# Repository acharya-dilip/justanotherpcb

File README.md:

# Justanotherpcb
This is a PCB that holds chaos press the button to get a glimpse of what it holds and beware it may jump or rant at you

# Materials List:
LED's x6
Resistor (220) x6
Resistor (4.7k) x4
Resistor (47k) x2
Transistor (NPN) x2
Capacitor (10uf) x2
Push Switch x1
Mini Motor Disc x1
Buzzer x1
CR2032 Battery Cell x2

# What Does It DO?
This small fella is powered by two batteries and holds 6 LED's a mini motor disc and a buzzer. With the help of an astable multivibrator constatly switches between two states when power is provided and while the switcherooo occurs LED's in groups of 3 flash on and off while the motor and the buzzer also turn on in small bursts in sync with the groups of LED's.

# Some Glimpses

# Made By DILIP ACHARYA
Slack ID: acharyamission6
Made in a ADHD Hyperfocus state.
He'll spend the next month in recovery mode
Peace!

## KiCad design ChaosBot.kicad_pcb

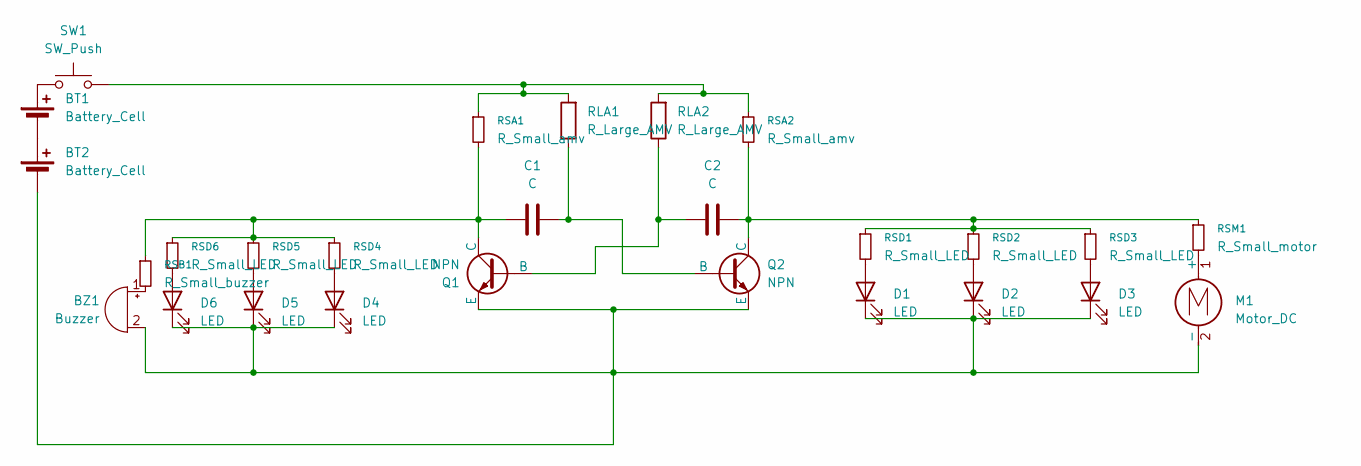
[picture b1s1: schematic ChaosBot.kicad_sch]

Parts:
BT1, BT2: Battery_Cell; BatteryHolder_Keystone_3034_1x20mm
BZ1: Buzzer; MagneticBuzzer_ProSignal_ABI-009-RC
C1, C2: C; CP_Radial_D8.0mm_P5.00mm
D1, D2, D3, D4, D5, D6: LED; LED_D5.0mm
M1: Motor_DC; PinHeader_1x02_P2.54mm_Vertical
Q1, Q2: NPN; TO-92L_HandSolder
RLA1, RLA2: R_Large_AMV; R_Axial_DIN0207_L6.3mm_D2.5mm_P7.62mm_Horizontal
RSA1, RSA2: R_Small_amv; R_Axial_DIN0207_L6.3mm_D2.5mm_P7.62mm_Horizontal
RSB1: R_Small_buzzer; R_Axial_DIN0207_L6.3mm_D2.5mm_P7.62mm_Horizontal
RSD1, RSD2, RSD3, RSD4, RSD5, RSD6: R_Small_LED; R_Axial_DIN0207_L6.3mm_D2.5mm_P7.62mm_Horizontal
RSM1: R_Small_motor; R_Axial_DIN0207_L6.3mm_D2.5mm_P7.62mm_Horizontal
SW1: SW_Push; SW_PUSH_6mm

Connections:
unnamed: BT1.1 (+), SW1.1
unnamed: BT1.2 (-), BT2.1 (+)
unnamed: BT2.2 (-), BZ1.2 (-), D1.1 (K), D2.1 (K), D3.1 (K), D4.1 (K), D5.1 (K), D6.1 (K), M1.2 (-), Q1.3 (E), Q2.3 (E)
unnamed: BZ1.1 (+), RSB1.2
unnamed: D1.2 (A), RSD1.2
unnamed: D2.2 (A), RSD2.2
unnamed: D3.2 (A), RSD3.2
unnamed: D4.2 (A), RSD4.2
unnamed: D5.2 (A), RSD5.2
unnamed: D6.2 (A), RSD6.2
unnamed: M1.1 (+), RSM1.2
unnamed: C2.1, Q1.2 (B), RLA2.1
unnamed: C1.1, Q1.1 (C), RSA1.2, RSB1.1, RSD4.1, RSD5.1, RSD6.1
unnamed: C1.2, Q2.2 (B), RLA1.1
unnamed: C2.2, Q2.1 (C), RSA2.2, RSD1.1, RSD2.1, RSD3.1, RSM1.1
unnamed: RLA1.2, RLA2.2, RSA1.1, RSA2.1, SW1.2

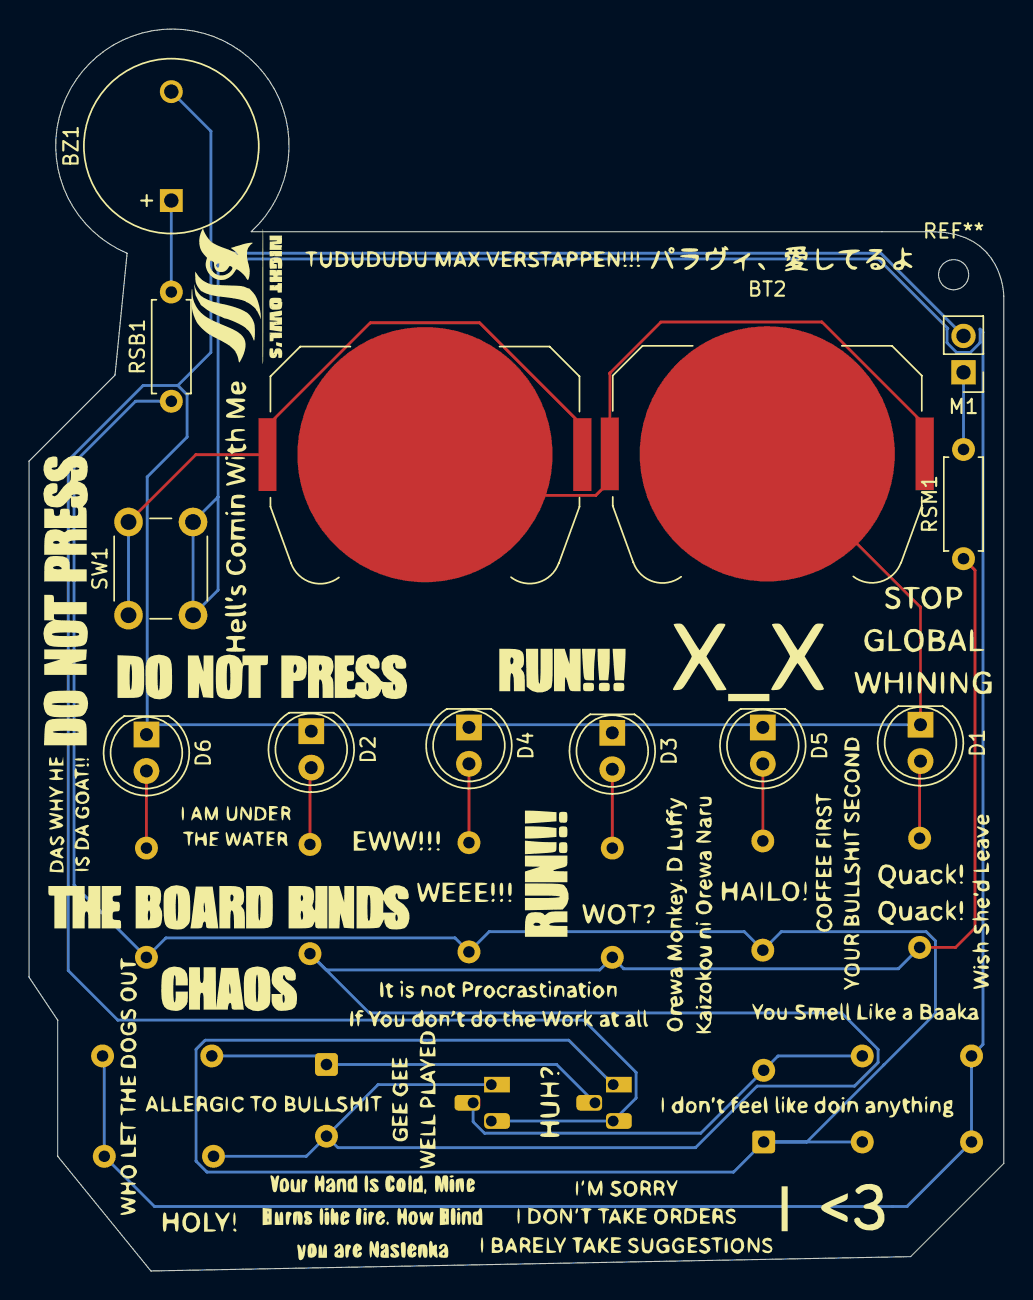
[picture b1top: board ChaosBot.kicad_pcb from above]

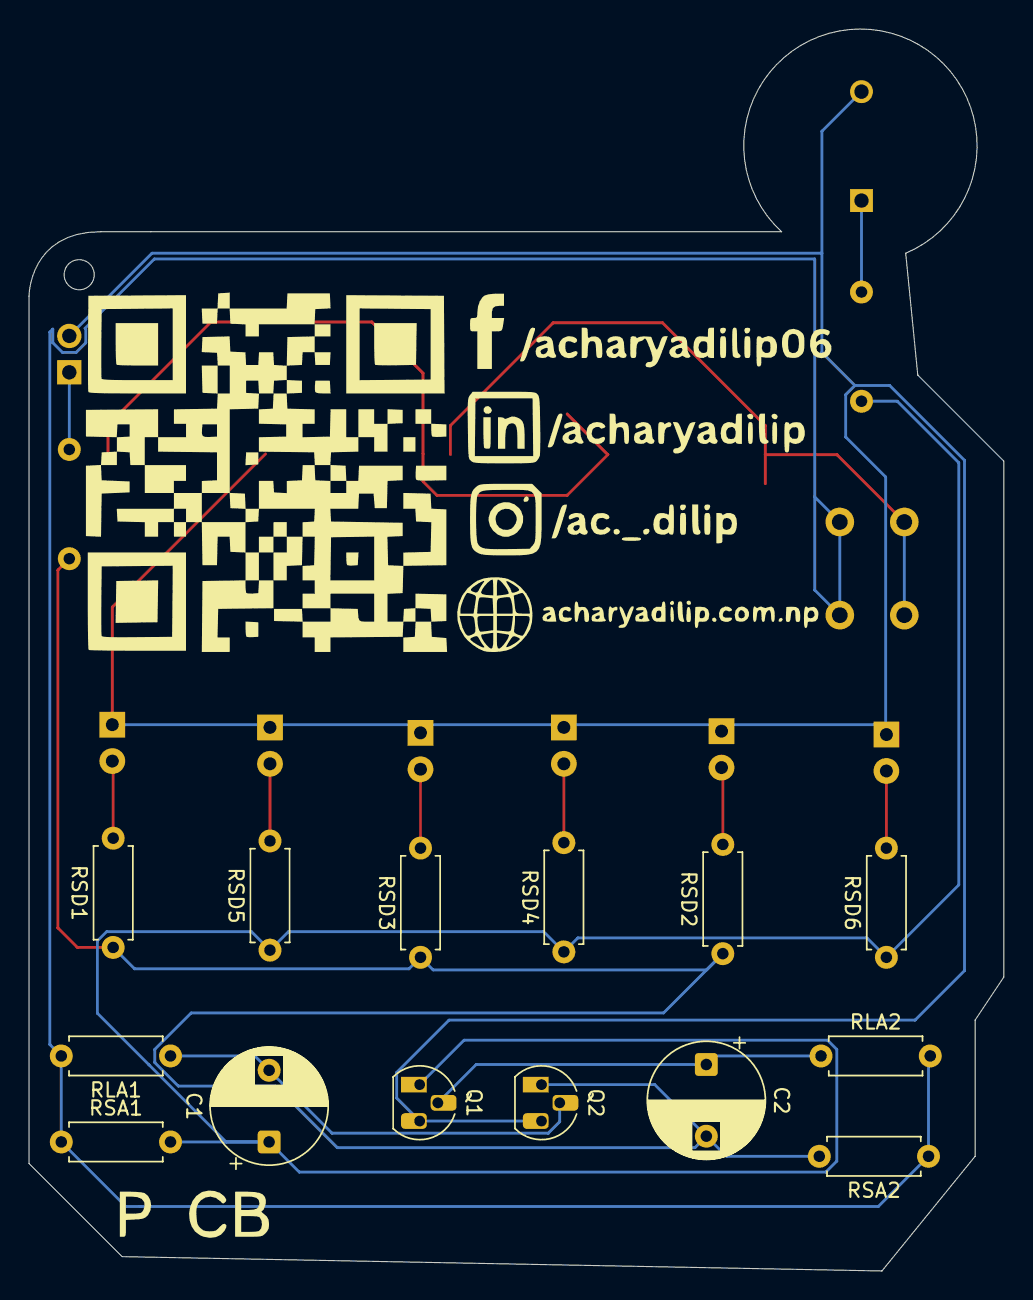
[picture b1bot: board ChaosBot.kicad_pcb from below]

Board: 2 copper layers, 68.0 x 86.6 mm, 27 parts (14 on the bottom side), 16 nets.

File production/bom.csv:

Designator,Footprint,Quantity,Value,LCSC Part #
"BT1, BT2",BatteryHolder_Keystone_3034_1x20mm,2,Battery_Cell,
BZ1,MagneticBuzzer_ProSignal_ABI-009-RC,1,Buzzer,
"C1, C2",CP_Radial_D8.0mm_P5.00mm,2,C,
"D1, D2, D3, D4, D5, D6",LED_D5.0mm,6,LED,
M1,PinHeader_1x02_P2.54mm_Vertical,1,Motor_DC,
"Q1, Q2",TO-92L_HandSolder,2,NPN,
"RLA1, RLA2",R_Axial_DIN0207_L6.3mm_D2.5mm_P7.62mm_Horizontal,2,R_Large_AMV,
"RSA1, RSA2",R_Axial_DIN0207_L6.3mm_D2.5mm_P7.62mm_Horizontal,2,R_Small_amv,
RSB1,R_Axial_DIN0207_L6.3mm_D2.5mm_P7.62mm_Horizontal,1,R_Small_buzzer,
"RSD1, RSD2, RSD3, RSD4, RSD5, RSD6",R_Axial_DIN0207_L6.3mm_D2.5mm_P7.62mm_Horizontal,6,R_Small_LED,
RSM1,R_Axial_DIN0207_L6.3mm_D2.5mm_P7.62mm_Horizontal,1,R_Small_motor,
SW1,SW_PUSH_6mm,1,SW_Push,

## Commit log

2025-06-03 Updated Readme.md with the PCB description
2025-06-03 Updated README.md with my intro
2025-06-03 Uploaded the Schematics and PCB design for the PCB
2025-06-03 Uploaded the correct files
2025-06-03 Update README.md with the photos of the circuit
2025-06-03 Uploaded the Falstad simulation
2025-06-04 Delete pcbway_production/2025-06-03-07-09-20 directory as it was outdated
    the battery holders were oriented the wrong way in the PCB
2025-06-04 Rotated the battery holder by 90 degree
    As it was not possbile to insert the batteries in the previous instance of the PCB
2025-06-04 Update README.md
    Corrected the image of the PCB after rotating the battery holders in the desgin by 90 degrees
2025-06-04 Rotated the battery by 180 degree
2025-06-04 test
2025-06-04 correct gerber files for the rotated PCB
2025-07-18 Added the Links in SS
2025-07-18 Updated the production files
